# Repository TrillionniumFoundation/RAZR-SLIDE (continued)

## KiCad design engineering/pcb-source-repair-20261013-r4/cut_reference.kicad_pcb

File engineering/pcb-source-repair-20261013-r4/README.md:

# Controlled component sources and first-cut reference PCB, R4

`manufacturing_go=false`. `phone_complete_PCB=false`. This is an **unpowered single-cut bench reference**, not a released phone, pack protector, charging board, or complete safety circuit. No physical sample was energized or tested.

Eight actual PDFs were obtained from TI and checked by size, PDF page count and SHA-256. `primary_source_facts.json` identifies exact revisions and official URLs. Raw vendor PDFs remain outside the repository. The attempted EU Motorola L3 mirror returned HTTP 405; no complete OEM schematic was obtained from it.

The sources provide real reference schematics, BOMs, board layouts and package dimensions for TPS25947, BQ25620/BQ25622 and TUSB2E22. They do not establish equivalence to the OEM PMIH0104, OEM battery connectors, OLED or phone repeater. The BQ297xx threshold variants are different: BQ29700's nominal overvoltage threshold is 4.275 V and BQ29704's is 4.425 V. Neither can be chosen for an unknown cell chemistry. A low-side pack protector also requires every external reference to use protected PACK_N, never raw CELL_N.

For USB, the controlled TUSB2E22 datasheet and eUSB2 design guide distinguish 1.2-V eUSB2 signaling from conventional USB2. The proposed eUSB2 side uses a TI-recommended 85-ohm differential channel and a continuous reference; USB2 specifies 90 ohms. This research does not downgrade or qualify the project's USB interface. Exact OEM repeater, SoC configuration, flex stackup, full-motion eye, skew and leakage remain missing. TUSB2E22's RESETB must respect its 1.8-V interface; it is not a direct 3.3-V GPIO connection.

## Actual repair

`cut_reference.kicad_sch` and `cut_reference.kicad_pcb` implement a real **TPS259470LRPW** first discharge cut. This exact variant is latch-off with adjustable OVLO and active current limit. TPS259470ARPW and TPS259474LRPW must not be substituted by name. AUXOFF pin 3 is an open-drain output; the owned R4 symbol corrects the R3 research symbol's input classification while retaining R3 unchanged.

The editable board is 29 × 24 × 1.6 mm with 15 annotated items, 30 unique schematic-to-board physical pins, 34 copper pads and 47 routed segments. The nominal RPW0010A corner L lands are represented by overlapping same-number copper rectangles. Their nominal extents come from drawing 4225183/A; their square corners and full-area paste differ from TI's R0.05 and 82/93% example stencil. These deviations, passive 0805 lands and all actual component MPNs require assembly/DFM qualification.

Bench hypotheses are explicit: 2.7–4.4 V input from an isolated laboratory source, external 3.3-V enable, 10-kohm default-off EN resistor, 1.69-kohm ILM resistor and 10-nF slew capacitor. The datasheet equation gives about 1.973 A nominal current limit, with the stated device tolerance; this is not a measured current rating or a phone selection. Input/output capacitors and current-carrying copper have not been thermally qualified. There is no actual phone control supply, pack protector, second cut, receiver, return diagnosis, charge path or USB path on this board. Schottky/TVS protection and source/load transient bounds remain unqualified. No cell node enters this board's net map.

## Native evidence

- Main/qian-qi: actual KiCad 7.0.11, one fresh `pcbnew` process per serialized board. Initial V1 reported **37 DRC violations**, including genuine VIN/GND and FLT/VIN copper conflicts, hole clearances and library/silkscreen defects. These source bytes and complete reports remain in the V1 archives. V2 physically relocates the capacitor, control traces and ground vias and corrects the library; DRC, unconnected pads and footprint errors are all **0** under unchanged 0.1-mm copper / 0.25-mm hole rules. No rule exclusions were added.
- Removing the ILM route from the same V2 board gives one dangling-track warning and **one actual unconnected pad**. The helper's process exit 0 only means it produced the report; the report's counts govern acceptance.
- Pocket4: actual KiCad 9.0.8 XML export and ERC exit 0, with **0 violations at all severities**. An independent reader matches all 30 unique board/schematic pins and all 10 exact-variant pin functions. TP1/TP2 explicitly represent external isolated laboratory power/reference, not implemented phone regulators.
- Main: actual native Gerber, drill, placement, SVG, board-only STEP and schematic exports exit 0. The seven Gerber layers, PTH/NPTH drill files and seven SMD placement rows are preserved under `native_main/v2/exports`. Validated source bytes remain unchanged before/after export.
- Cloud: the entire exported STEP root is independently checked using the existing strict payload validator. It has one valid positive solid, 29 × 24 × 1.6-mm bounds and 1107.1660182454489 mm³ volume, matching the board with eight 0.8-mm pad holes. KiCad7's STEP omits the seven via bores and every unselected component 3D model. It is **not a full assembly** or a fit/thermal/insulation certificate.

`operator_process_receipts.json` retains native process results, child results and runtime failures. Pocket4's KiCad9 PCB plugin originally lacked OCC dependencies. Private dependency download attempts timed out; KiCad9 PCB DRC was not claimed. The actual board DRC/exports instead use the existing native KiCad7 engine on Main. A shell ending with `mkdir` and a Python report wrapper may exit 0 despite an earlier child failure; those failures remain visible. Full reports were recovered in version-pinned binary archives and checked by whole-file SHA-256.

`copper_only_preview.png` was visually checked against the native SVG. `pcb_preview.png` preserves the dense native F.Fab overlay for inspection; it is not an assembly drawing. The native editable schematic remains the authoritative connection drawing. Inkscape's startup GtkRecentManager warning was observed with successful exit 0.

The complete phone PCB, controlled OLED/FPC input, real assembly and physical capture/retraction/battery/USB/OLED qualifications remain open. No supplier message, NDA, order or production release was submitted. Fixed product constraints remain equal A/B external size, one approximately 7-inch OLED, 79.75-mm upward stroke and 8.2-mm normal seating, A battery priority and **4700-mAh total system target**.

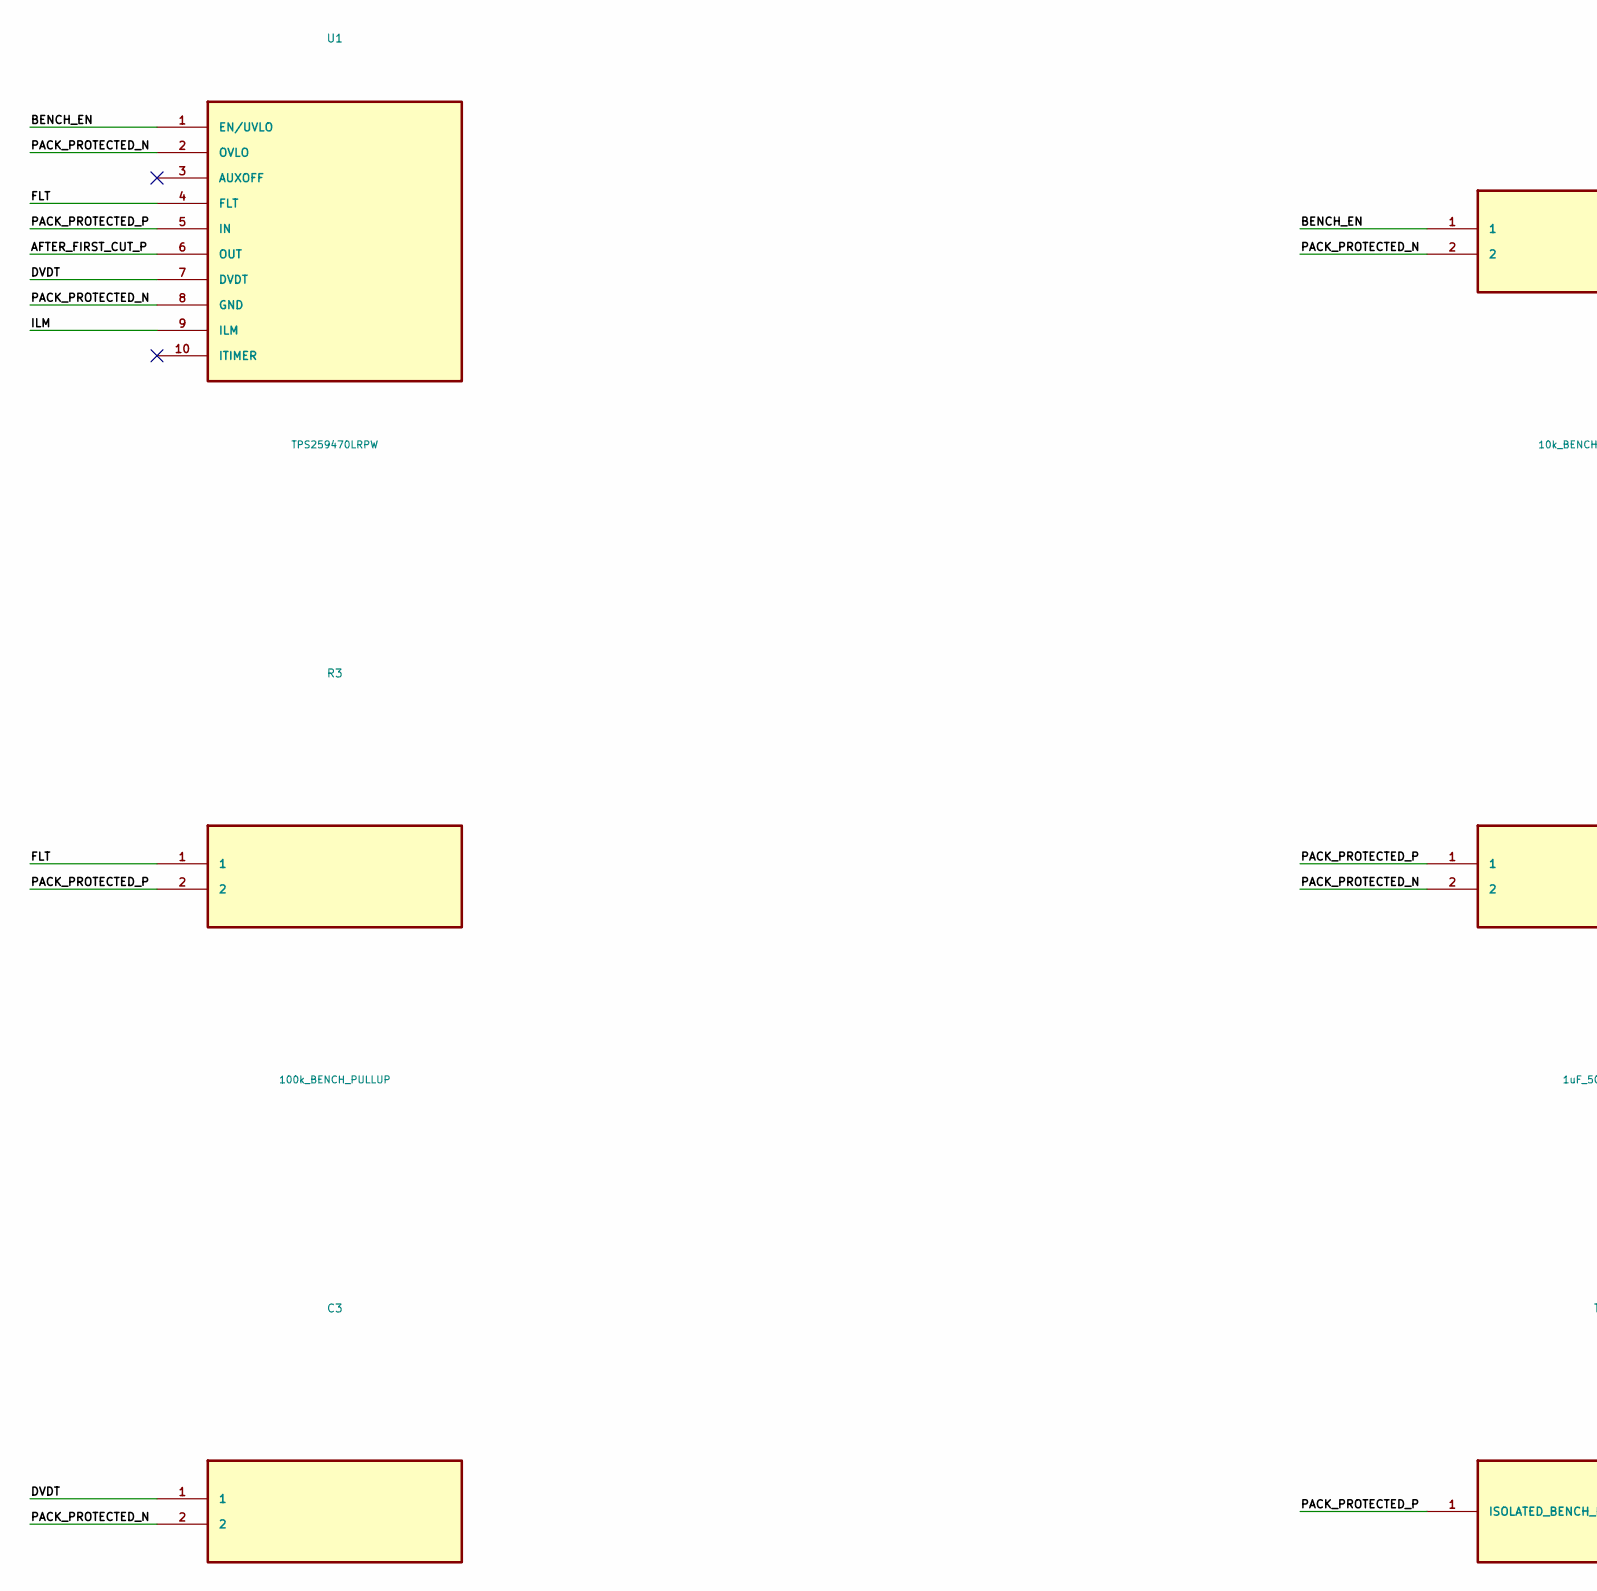
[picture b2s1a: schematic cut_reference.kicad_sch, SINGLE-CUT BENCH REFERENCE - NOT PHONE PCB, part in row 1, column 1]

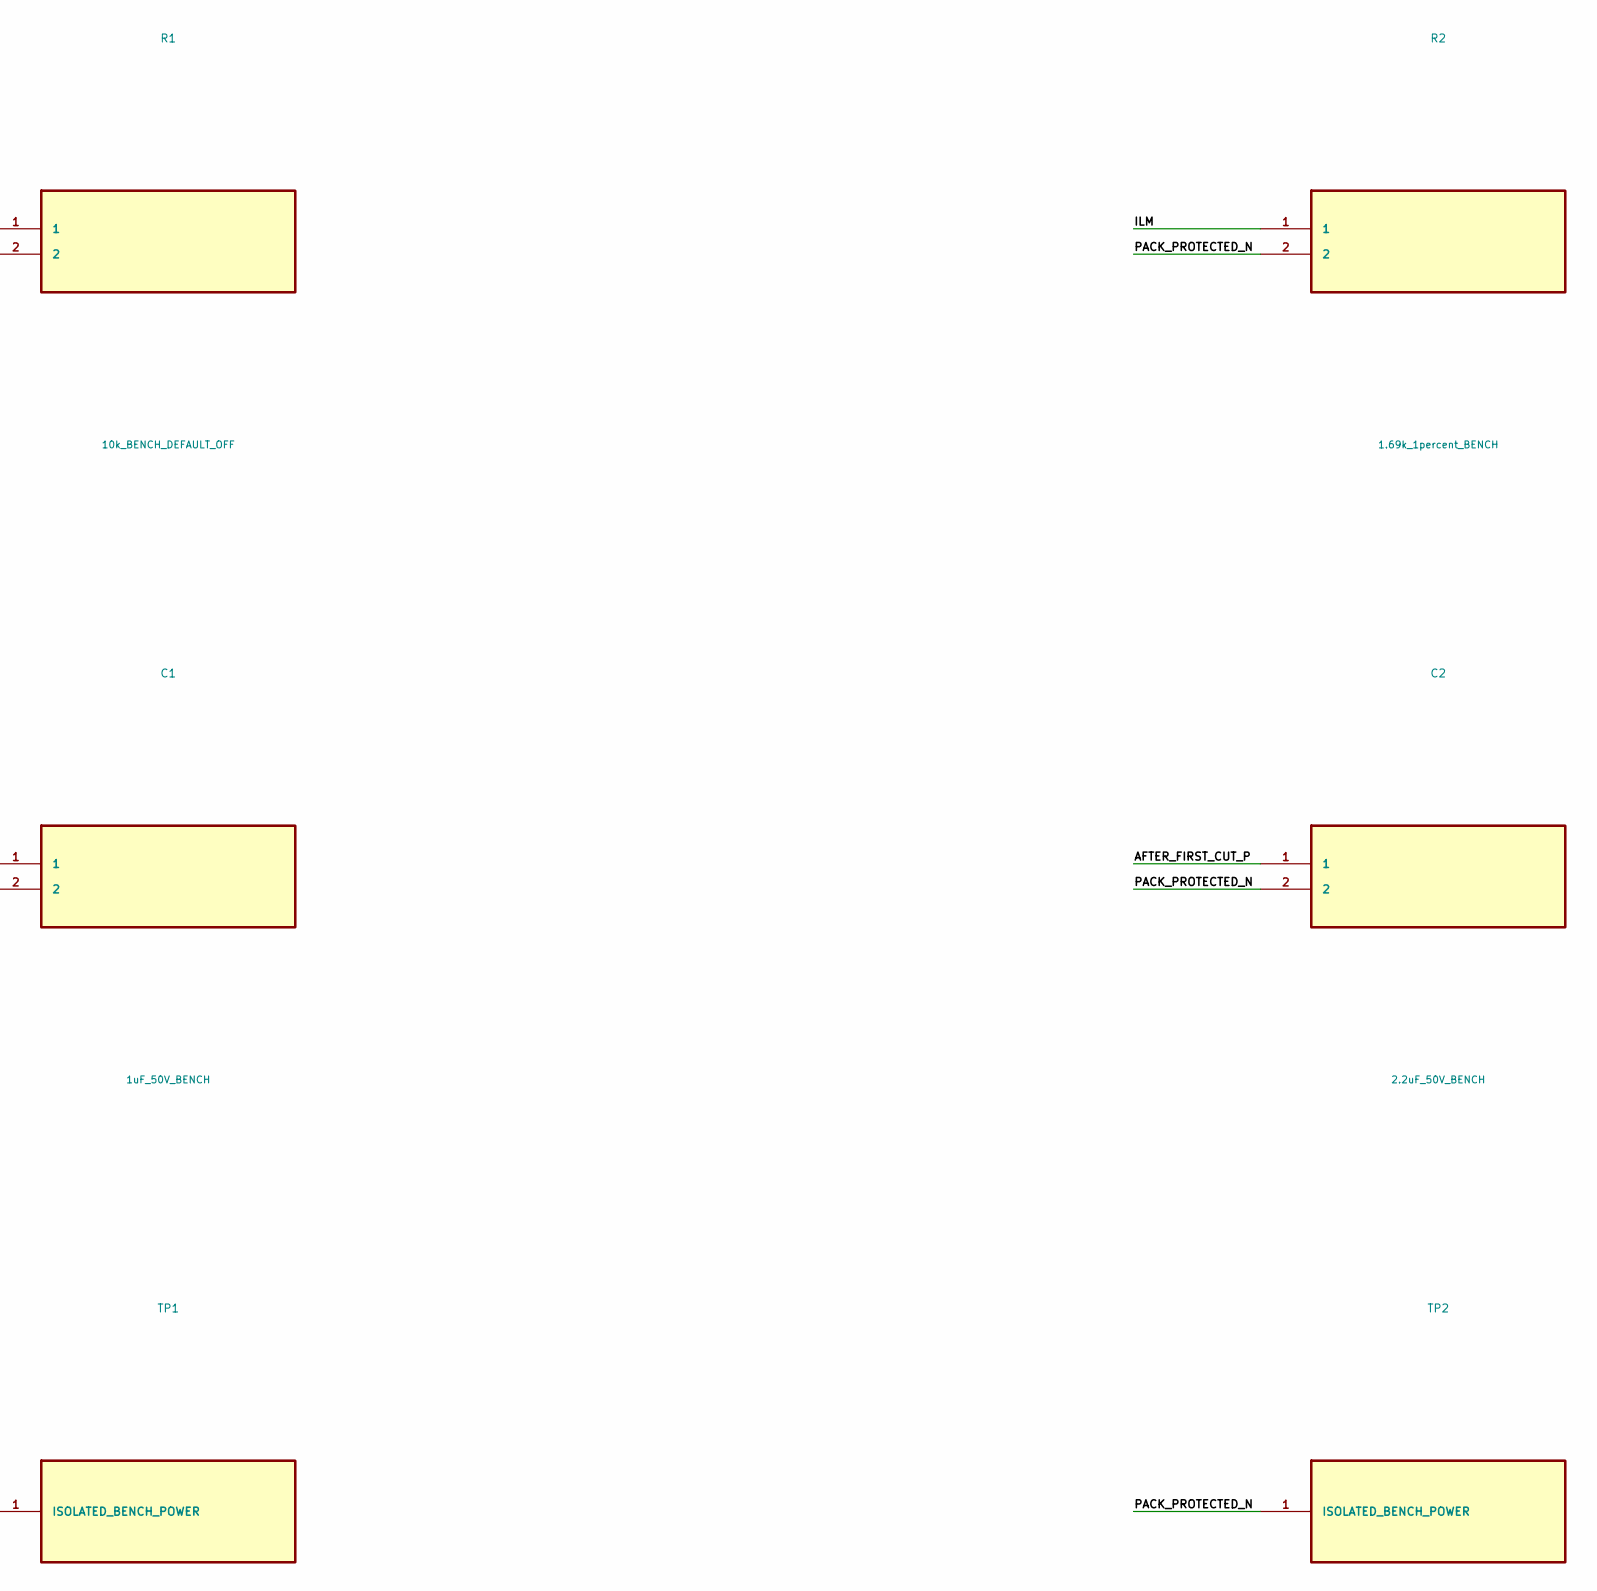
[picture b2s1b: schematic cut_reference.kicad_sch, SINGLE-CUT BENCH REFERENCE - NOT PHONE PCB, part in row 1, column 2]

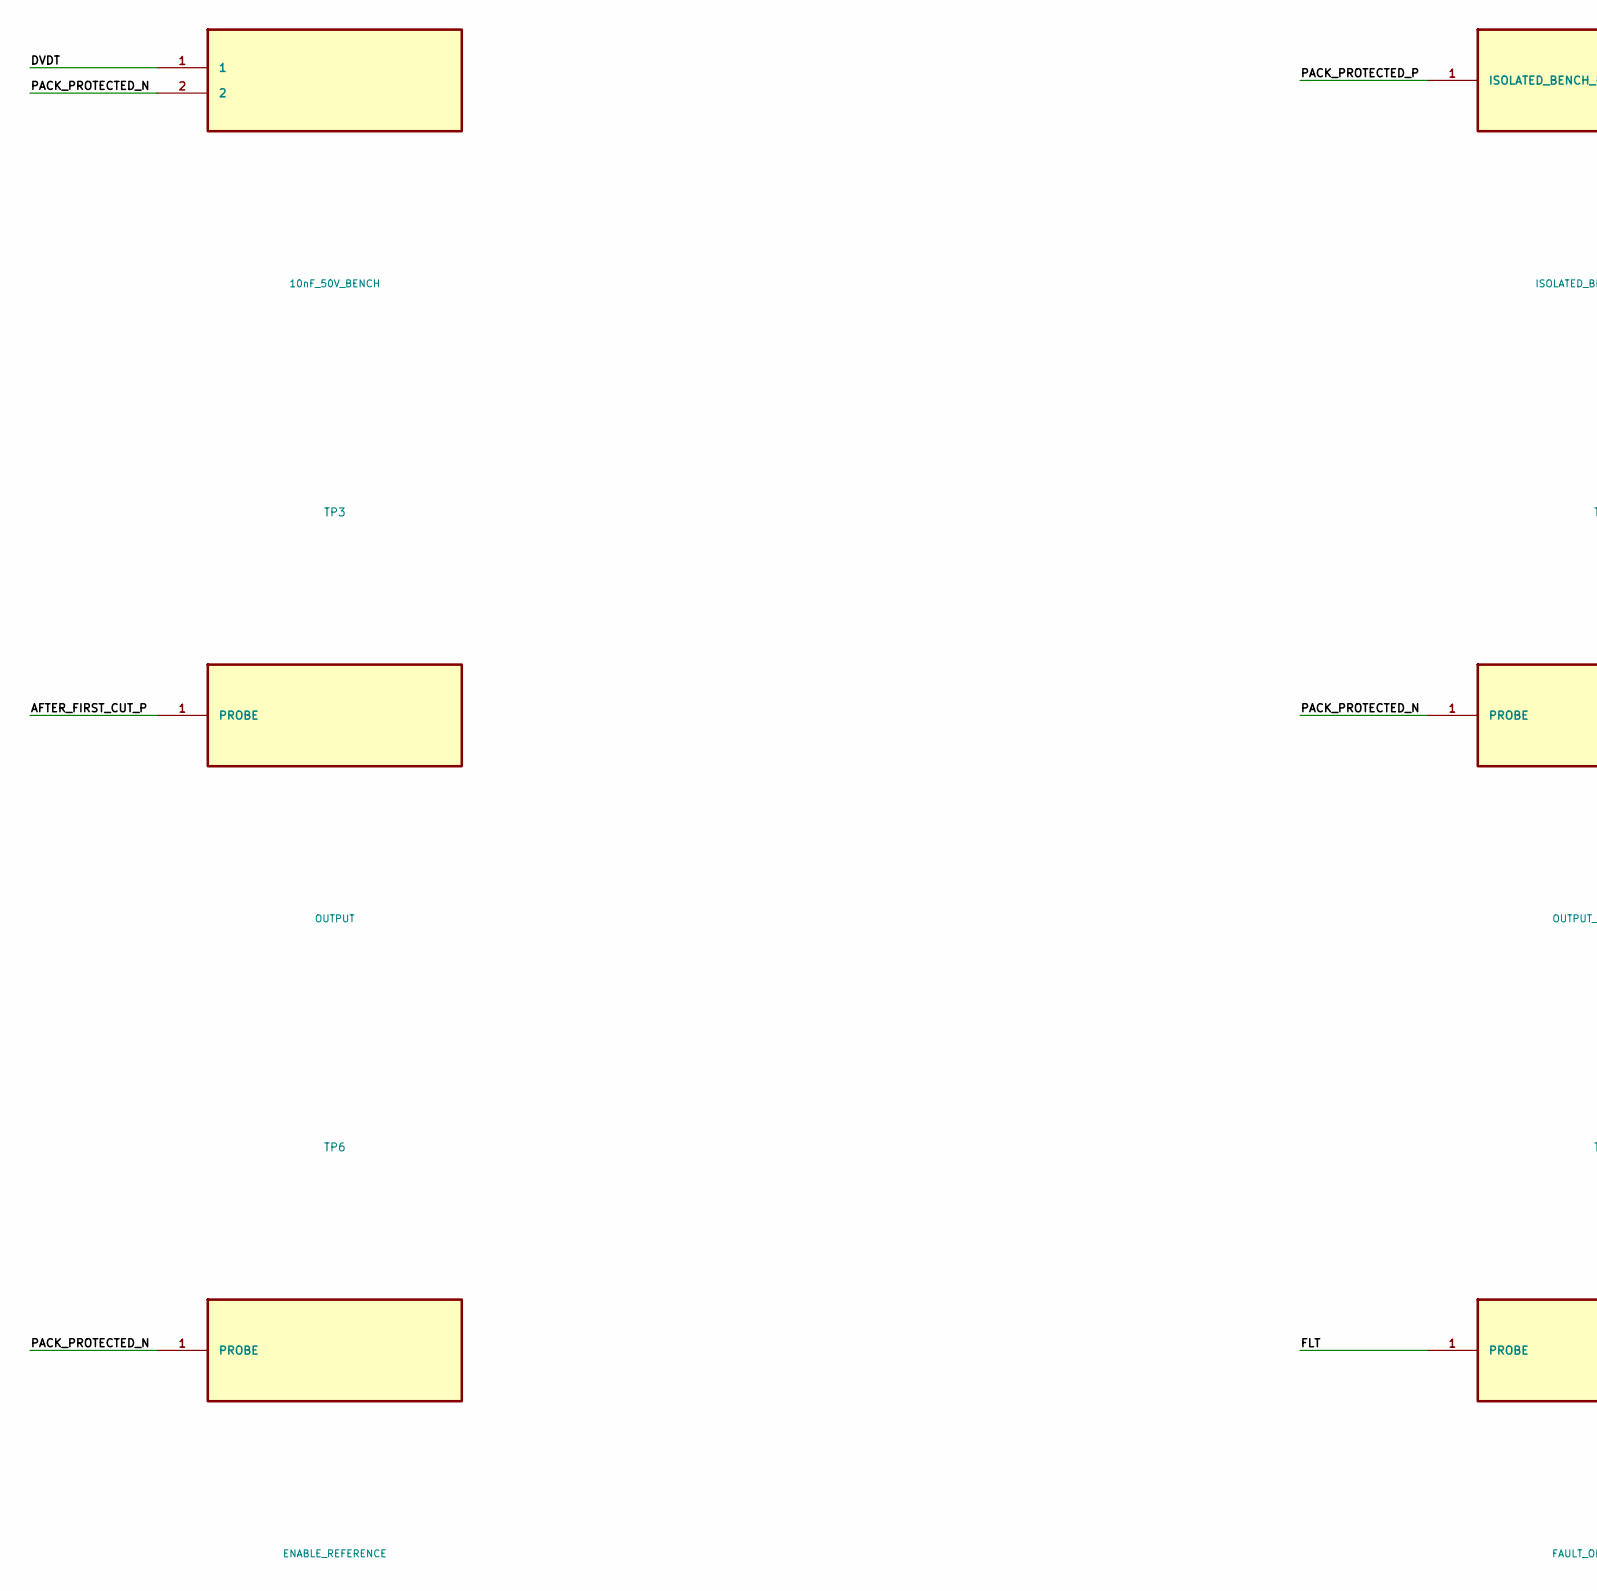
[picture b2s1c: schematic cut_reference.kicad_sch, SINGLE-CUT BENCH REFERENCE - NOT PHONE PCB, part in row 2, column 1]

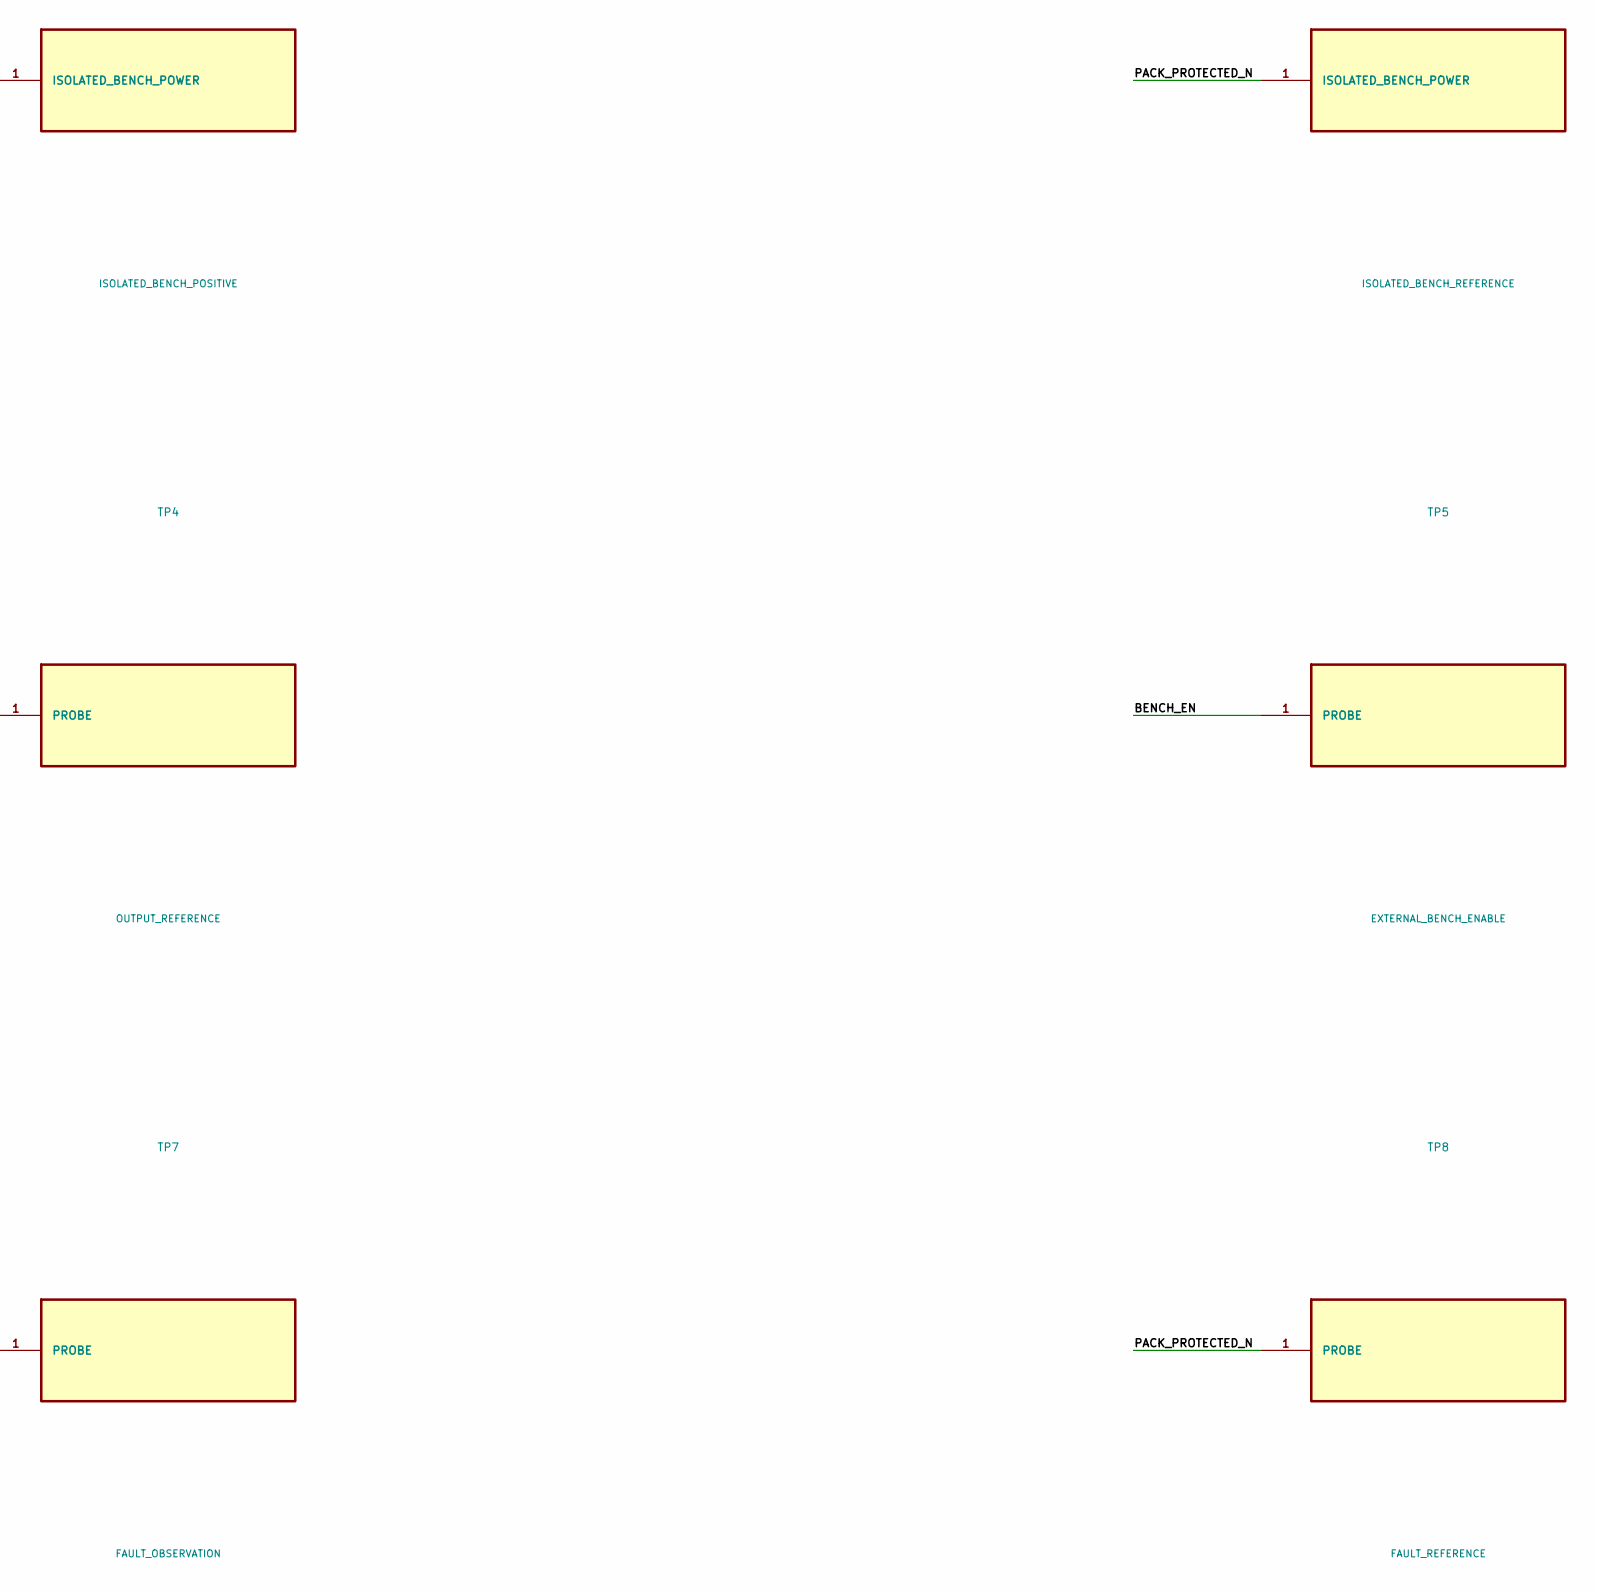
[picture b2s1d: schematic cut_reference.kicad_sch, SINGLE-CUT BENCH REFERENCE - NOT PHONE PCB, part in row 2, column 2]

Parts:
C1: 1uF_50V_BENCH; Passive_0805_BENCH
C2: 2.2uF_50V_BENCH; Passive_0805_BENCH
C3: 10nF_50V_BENCH; Passive_0805_BENCH
R1: 10k_BENCH_DEFAULT_OFF; Passive_0805_Vertical_BENCH
R2: 1.69k_1percent_BENCH; Passive_0805_BENCH
R3: 100k_BENCH_PULLUP; Passive_0805_BENCH
TP1: ISOLATED_BENCH_POSITIVE; Probe_1p8mm
TP2: ISOLATED_BENCH_REFERENCE; Probe_1p8mm
TP3: OUTPUT; Probe_1p8mm
TP4: OUTPUT_REFERENCE; Probe_1p8mm
TP5: EXTERNAL_BENCH_ENABLE; Probe_1p8mm
TP6: ENABLE_REFERENCE; Probe_1p8mm
TP7: FAULT_OBSERVATION; Probe_1p8mm
TP8: FAULT_REFERENCE; Probe_1p8mm
U1: TPS259470LRPW; RPW0010A_OWNED_NOMINAL

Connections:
AFTER_FIRST_CUT_P: C2.1, TP3.1, U1.6 (OUT)
BENCH_EN: R1.1, TP5.1, U1.1 (EN/UVLO)
DVDT: C3.1, U1.7 (DVDT)
FLT: R3.1, TP7.1, U1.4 (FLT)
ILM: R2.1, U1.9 (ILM)
PACK_PROTECTED_N: C1.2, C2.2, C3.2, R1.2, R2.2, TP2.1, TP4.1, TP6.1, TP8.1, U1.2 (OVLO), U1.8 (GND)
PACK_PROTECTED_P: C1.1, R3.2, TP1.1, U1.5 (IN)

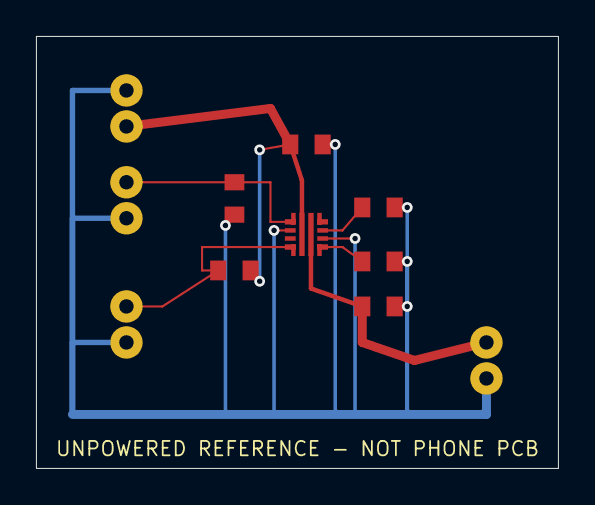
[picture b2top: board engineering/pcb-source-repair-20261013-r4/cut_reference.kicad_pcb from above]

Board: 2 copper layers, 29.0 x 24.0 mm, 15 parts (0 on the bottom side), 7 nets.

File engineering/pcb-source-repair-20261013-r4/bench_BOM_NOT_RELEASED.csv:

ref,part,value,footprint,MPN_selected_for_phone,physical_qualified
U1,TPS259470LRPW,TPS259470LRPW,RPW0010A_OWNED_NOMINAL,False,False
R1,R,10k_BENCH_DEFAULT_OFF,Passive_0805_Vertical_BENCH,False,False
R2,R,1.69k_1percent_BENCH,Passive_0805_BENCH,False,False
R3,R,100k_BENCH_PULLUP,Passive_0805_BENCH,False,False
C1,C,1uF_50V_BENCH,Passive_0805_BENCH,False,False
C2,C,2.2uF_50V_BENCH,Passive_0805_BENCH,False,False
C3,C,10nF_50V_BENCH,Passive_0805_BENCH,False,False
TP1,BenchSource,ISOLATED_BENCH_POSITIVE,Probe_1p8mm,False,False
TP2,BenchSource,ISOLATED_BENCH_REFERENCE,Probe_1p8mm,False,False
TP3,Probe,OUTPUT,Probe_1p8mm,False,False
TP4,Probe,OUTPUT_REFERENCE,Probe_1p8mm,False,False
TP5,Probe,EXTERNAL_BENCH_ENABLE,Probe_1p8mm,False,False
TP6,Probe,ENABLE_REFERENCE,Probe_1p8mm,False,False
TP7,Probe,FAULT_OBSERVATION,Probe_1p8mm,False,False
TP8,Probe,FAULT_REFERENCE,Probe_1p8mm,False,False

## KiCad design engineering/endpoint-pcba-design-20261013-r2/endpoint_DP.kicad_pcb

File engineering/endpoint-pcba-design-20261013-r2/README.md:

# BM28 static continuity coupon PCBA candidates

Two actual KiCad schematic/PCB projects route every independent BM28 coordinate
site to a probe hole. Native KiCad 7.0.11 loads both boards, reports zero DRC
violations, zero unconnected pads and zero footprint errors, and exports the
research Gerbers, drills, placement and BOM. Native schematic XML and native
board data independently agree on all 26 electrical nets per board. This is a
passive continuity-coupon design candidate, not the complete phone PCB.
Independent pocket4 KiCad 9.0.8 native ERC also reports zero violations on both
schematics after a real off-grid failure was corrected.

`manufacturing_go=false` and `coupon_fabrication_go=false`. Material, copper
weight, soldermask process, mating orientation and real assembly qualification
remain unverified. Nothing was ordered, fabricated, energized or measured on a
physical coupon in this work.

## Actual source and output files

Open `endpoint_DP.kicad_pro` or `endpoint_DS.kicad_pro`; each has a native
`.kicad_sch`, `.kicad_pcb`, local footprint table and owned symbol library. The
schematic contains one connector and 26 passive probe features. Probe features
are PCB copper and plated holes, not 26 discrete parts to purchase.

| Design feature | Each board |
| --- | ---: |
| Board outline, research hypothesis | 40 x 36 mm |
| Thickness, research hypothesis | 0.8 mm |
| Copper layers | 2 |
| Signal coordinate sites | 24 |
| Fitting terminal identities | 2 |
| Connector copper lands | 28 |
| Probe holes / copper features | 26 / 26 |
| Probe drill / pad diameter | 0.5 / 1.0 mm |
| Asymmetric fixture datum NPTH | 3 x 2.0 mm |
| Total native pad objects, including NPTH | 57 |
| Native track segments | 80, on F.Cu |
| Proposed minimum clearance / signal trace | 0.10 / 0.10 mm |

The 26 plated probe holes expose copper on both faces, allowing access from the
outside faces after two boards mate. A first layout with only front-side probe
pads was corrected because the inward faces would impede probing. No impedance,
current capability, high-speed operation or manufacturing process is qualified
by the above dimensions.

The two footprint copies in `RAZR_ENDPOINT_RESEARCH.pretty` are byte-identical
to the frozen prior endpoint source. `RAZR_ENDPOINT_ASSEMBLY.pretty` changes
only research BOM/placement exclusion flags. Board-instance reference text and
position are annotations; nominal copper, independent stencil rectangles and
the DS under-body copper/track/via/pad keepout stay unchanged. The DS keepout is
transformed into the actual board datum and checked by the native engine at
`[97.635, 99.410, 4.730, 1.180]` mm bounding rectangle. DP's 7.0 x 1.9-mm
minimum no-obstruction drawing is preserved, including its distinction from
an all-layer copper prohibition through its own lands.

## Coordinate identity and assembly datum

`C01` through `C26` mean continuity only. The supplier provides no pin-1
designation for these mechanically unpolarized connectors. `S_NEG_00` through
`S_POS_11`, `P_L` and `P_R` are our coordinate IDs, never invented supplier pin
numbers or Motorola net assignments. Two lands on each fitting share one
terminal ID. For example, our chosen pairing maps DP `S_NEG_00` to DS
`S_POS_00`; DP TP01 and DS TP13 both carry C01. All 26 pairings and actual probe
IDs are in `mating_site_map.json`.

The upper DP board uses the derived X-axis 180-degree transform
`diag(1,-1,-1)` with nominal 0.6-mm mating-plane translation. Native PCB-read
hole coordinates match all three DS datum holes under that transform and fail
the opposite Y-axis 180-degree orientation. This is a fixture datum proposal:
matching locating pins and a physical assembly trial are still required.
Silkscreen or intrinsic connector polarity alone does not prevent mis-mating.
The nominal translation is not the entire installed stack height.

New Motorola service evidence identifies SCA8D57591 24-pin/H0.6-mm/pitch0.35-mm
receptacles but does not give a Hirose series part number. Equal pitch, height
and pin count do not prove BM28 compatibility. No OEM assignment was transferred
to this coupon. See `../controlled-input-recovery-20261013-r2` for that evidence.

## Native evidence and retained counterexamples

`native_pcba_receipt.json` contains engine-read pads, tracks, hole coordinates,
the DS rule area, native netlists and exact export hashes. `native_execution_proof.json`
records the authoritative remote process exit, log offsets and transferred
archive SHA-256. `verify_native_pcba.py` never imports the builder.

The real missing-route negative control reports an unconnected pad. The actual
C01-to-C02 copper bridge reports four fatal native errors, including 0.0000-mm
cross-net copper clearance. Native DRC's Boolean report-writing return was
never treated as a passing result; report contents must show zero violations.
The rejected native boards and reports are retained.
Each DRC now runs in its own fresh native process from a serialized board and
checks that the proposed 0.10-mm clearance / 0.25-mm hole rules actually load.
The in-memory multiple-board path produced only one mask error on the same
shorted board; independent reload restored the four fatal errors. The exact
engine cause is not established. Both reports remain available; no constraint
or negative-control assertion was relaxed to accept the incomplete check.

Other retained failures include the initial 83/84 DRC warnings, an incorrect
native API call, local/global net namespace mismatch, missing export directories,
and a verifier's wrong assumption about a KiCad version's short-error label.
SVG output exposed another real failure: PCB SVG output needs an explicit file
name; a directory argument returned zero without replacing an old preview.
Current verification requires separate native board and schematic files,
existence and unequal byte hashes. Stale parent-directory previews are retained
as `REJECTED_svg_stale_parent_*`.

`verify_exports.py` independently parses the actual Gerber stencil polygons and
PTH/NPTH coordinates, checks 24 signal plus four fitting rectangles, checks all
probe and datum holes against native PCB data, and verifies that placement
contains only J1. `independent_export_receipt.json` records these results. The
absolute native export uses `x=board_x, y=-board_y`; negative export Y is a
coordinate convention.

The KiCad7 CLI does not have an ERC command, so the KiCad7 receipt truthfully
records `native_ERC_executed=false`. `pocket4_ERC_receipt.json` and the two
`endpoint_*_native_ERC.json` files provide the separate actual KiCad9 ERC runs:
zero errors, warnings and exclusions on both schematics, exit zero, and all 13
frozen input SHA-256 values unchanged. The initial real ERC found 79 off-grid
warnings per board. Symbol origins, label anchors and wire ends were moved to
the standard 1.27-mm connection grid; board geometry and all 26 nets stayed
unchanged. The original 13 input files are preserved in
`REJECTED_ERC_offgrid_inputs_v1.tar.gz`; failure reports reside in the adjoining
qualification evidence. `ERC_INPUTS_FROZEN.json` binds the repaired inputs.
Actual rendered schematic review then found overlapping probe references and
values despite the zero ERC result. Row pitch was increased to 5.08 mm, duplicate
displayed pin numbers hidden, connector attributes moved outside the symbol,
and probe reference/value text placed in separate columns. Current native7
exact-net verification and current independent native9 ERC both pass on those
final readable source hashes. The earlier ERC-pass source package and the real
overlap SVG/PNG are retained. `verification_summary.json` binds the current
combined result; `visual_review.json` records inspection of both final native
schematics and both final native board images.

## Remaining physical and controlled-input blockers

The original DP 6.32-MIN versus guideline 6.32-MAX authority conflict and DS
paste-volume discrepancy remain unresolved. Nominal 0.08-mm stencil arithmetic
is not a process approval. Zero soldermask expansion is explicitly an unqualified
hypothesis, not a supplier recommendation. Actual board process capability,
reflow/inspection plan, mating force and orientation, locator fit, buffer/preload,
connector availability and physical continuity measurements remain absent.

The three datum holes do not qualify a moving FPC strain-release design. The
flex stack, copper neutral axis, clamping details, voltage/current assignments,
USB lane routing, batteries, OEM electronics and final phone PCB are not present
in this coupon. They remain separate unresolved engineering inputs.

## Reproduce

Generate candidates with `python3 build_pcba.py`. In qian-qi's previously
extracted KiCad7 runtime, set `LD_LIBRARY_PATH` and `PYTHONPATH` to its preserved
`extracted/usr/lib/x86_64-linux-gnu` and `extracted/usr/lib/python3/dist-packages`,
and set `RAZR_KICAD_CLI` to that runtime's `extracted/usr/bin/kicad-cli`.
Run `python3 verify_native_pcba.py`, then `python3 verify_exports.py`. These
scripts create only local engineering evidence and research export files.

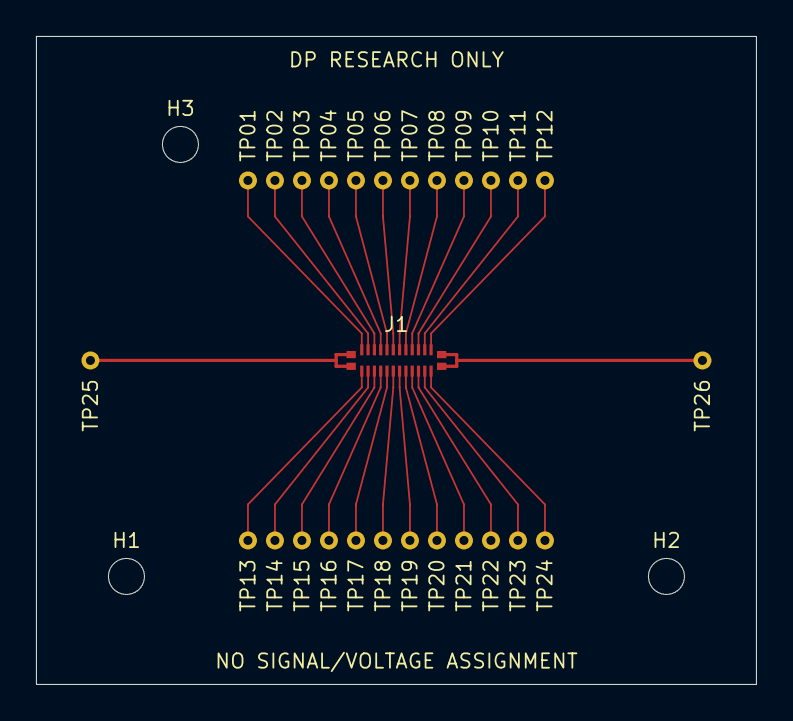
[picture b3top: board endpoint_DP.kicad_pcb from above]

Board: 2 copper layers, 40.0 x 36.0 mm, 30 parts (0 on the bottom side), 26 nets.

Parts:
H1, H2, H3: FIXTURE_DATUM_UNQUALIFIED; Datum_2mm_NPTH
J1: BM28_24DP_RESEARCH; Hirose_BM28B0.6-24DP_2-0.35V_53_RESEARCH_PHYSICAL_SITES
TP01: PROBE_ONLY_S_NEG_00; ProbePad_1mm_NO_PASTE
TP02: PROBE_ONLY_S_NEG_01; ProbePad_1mm_NO_PASTE
TP03: PROBE_ONLY_S_NEG_02; ProbePad_1mm_NO_PASTE
TP04: PROBE_ONLY_S_NEG_03; ProbePad_1mm_NO_PASTE
TP05: PROBE_ONLY_S_NEG_04; ProbePad_1mm_NO_PASTE
TP06: PROBE_ONLY_S_NEG_05; ProbePad_1mm_NO_PASTE
TP07: PROBE_ONLY_S_NEG_06; ProbePad_1mm_NO_PASTE
TP08: PROBE_ONLY_S_NEG_07; ProbePad_1mm_NO_PASTE
TP09: PROBE_ONLY_S_NEG_08; ProbePad_1mm_NO_PASTE
TP10: PROBE_ONLY_S_NEG_09; ProbePad_1mm_NO_PASTE
TP11: PROBE_ONLY_S_NEG_10; ProbePad_1mm_NO_PASTE
TP12: PROBE_ONLY_S_NEG_11; ProbePad_1mm_NO_PASTE
TP13: PROBE_ONLY_S_POS_00; ProbePad_1mm_NO_PASTE
TP14: PROBE_ONLY_S_POS_01; ProbePad_1mm_NO_PASTE
TP15: PROBE_ONLY_S_POS_02; ProbePad_1mm_NO_PASTE
TP16: PROBE_ONLY_S_POS_03; ProbePad_1mm_NO_PASTE
TP17: PROBE_ONLY_S_POS_04; ProbePad_1mm_NO_PASTE
TP18: PROBE_ONLY_S_POS_05; ProbePad_1mm_NO_PASTE
TP19: PROBE_ONLY_S_POS_06; ProbePad_1mm_NO_PASTE
TP20: PROBE_ONLY_S_POS_07; ProbePad_1mm_NO_PASTE
TP21: PROBE_ONLY_S_POS_08; ProbePad_1mm_NO_PASTE
TP22: PROBE_ONLY_S_POS_09; ProbePad_1mm_NO_PASTE
TP23: PROBE_ONLY_S_POS_10; ProbePad_1mm_NO_PASTE
TP24: PROBE_ONLY_S_POS_11; ProbePad_1mm_NO_PASTE
TP25: PROBE_ONLY_P_L; ProbePad_1mm_NO_PASTE
TP26: PROBE_ONLY_P_R; ProbePad_1mm_NO_PASTE

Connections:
C01: J1.S_NEG_00, TP01.1
C02: J1.S_NEG_01, TP02.1
C03: J1.S_NEG_02, TP03.1
C04: J1.S_NEG_03, TP04.1
C05: J1.S_NEG_04, TP05.1
C06: J1.S_NEG_05, TP06.1
C07: J1.S_NEG_06, TP07.1
C08: J1.S_NEG_07, TP08.1
C09: J1.S_NEG_08, TP09.1
C10: J1.S_NEG_09, TP10.1
C11: J1.S_NEG_10, TP11.1
C12: J1.S_NEG_11, TP12.1
C13: J1.S_POS_00, TP13.1
C14: J1.S_POS_01, TP14.1
C15: J1.S_POS_02, TP15.1
C16: J1.S_POS_03, TP16.1
C17: J1.S_POS_04, TP17.1
C18: J1.S_POS_05, TP18.1
C19: J1.S_POS_06, TP19.1
C20: J1.S_POS_07, TP20.1
C21: J1.S_POS_08, TP21.1
C22: J1.S_POS_09, TP22.1
C23: J1.S_POS_10, TP23.1
C24: J1.S_POS_11, TP24.1
C25: J1.P_L, TP25.1
C26: J1.P_R, TP26.1

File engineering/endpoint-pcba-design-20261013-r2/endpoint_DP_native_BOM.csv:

reference,value,footprint,procurement_role
J1,BM28_24DP_COORDINATE_SITES,RAZR_ENDPOINT_RESEARCH:Hirose_BM28B0.6-24DP_2-0.35V_53_RESEARCH_PHYSICAL_SITES,connector only
TP01,PROBE_S_NEG_00,Owned_Coupon:ProbePad_1mm_NO_PASTE,PCB probe feature; no discrete part
TP02,PROBE_S_NEG_01,Owned_Coupon:ProbePad_1mm_NO_PASTE,PCB probe feature; no discrete part
TP03,PROBE_S_NEG_02,Owned_Coupon:ProbePad_1mm_NO_PASTE,PCB probe feature; no discrete part
TP04,PROBE_S_NEG_03,Owned_Coupon:ProbePad_1mm_NO_PASTE,PCB probe feature; no discrete part
TP05,PROBE_S_NEG_04,Owned_Coupon:ProbePad_1mm_NO_PASTE,PCB probe feature; no discrete part
TP06,PROBE_S_NEG_05,Owned_Coupon:ProbePad_1mm_NO_PASTE,PCB probe feature; no discrete part
TP07,PROBE_S_NEG_06,Owned_Coupon:ProbePad_1mm_NO_PASTE,PCB probe feature; no discrete part
TP08,PROBE_S_NEG_07,Owned_Coupon:ProbePad_1mm_NO_PASTE,PCB probe feature; no discrete part
TP09,PROBE_S_NEG_08,Owned_Coupon:ProbePad_1mm_NO_PASTE,PCB probe feature; no discrete part
TP10,PROBE_S_NEG_09,Owned_Coupon:ProbePad_1mm_NO_PASTE,PCB probe feature; no discrete part
TP11,PROBE_S_NEG_10,Owned_Coupon:ProbePad_1mm_NO_PASTE,PCB probe feature; no discrete part
TP12,PROBE_S_NEG_11,Owned_Coupon:ProbePad_1mm_NO_PASTE,PCB probe feature; no discrete part
TP13,PROBE_S_POS_00,Owned_Coupon:ProbePad_1mm_NO_PASTE,PCB probe feature; no discrete part
TP14,PROBE_S_POS_01,Owned_Coupon:ProbePad_1mm_NO_PASTE,PCB probe feature; no discrete part
TP15,PROBE_S_POS_02,Owned_Coupon:ProbePad_1mm_NO_PASTE,PCB probe feature; no discrete part
TP16,PROBE_S_POS_03,Owned_Coupon:ProbePad_1mm_NO_PASTE,PCB probe feature; no discrete part
TP17,PROBE_S_POS_04,Owned_Coupon:ProbePad_1mm_NO_PASTE,PCB probe feature; no discrete part
TP18,PROBE_S_POS_05,Owned_Coupon:ProbePad_1mm_NO_PASTE,PCB probe feature; no discrete part
TP19,PROBE_S_POS_06,Owned_Coupon:ProbePad_1mm_NO_PASTE,PCB probe feature; no discrete part
TP20,PROBE_S_POS_07,Owned_Coupon:ProbePad_1mm_NO_PASTE,PCB probe feature; no discrete part
TP21,PROBE_S_POS_08,Owned_Coupon:ProbePad_1mm_NO_PASTE,PCB probe feature; no discrete part
TP22,PROBE_S_POS_09,Owned_Coupon:ProbePad_1mm_NO_PASTE,PCB probe feature; no discrete part
TP23,PROBE_S_POS_10,Owned_Coupon:ProbePad_1mm_NO_PASTE,PCB probe feature; no discrete part
TP24,PROBE_S_POS_11,Owned_Coupon:ProbePad_1mm_NO_PASTE,PCB probe feature; no discrete part
TP25,PROBE_P_L,Owned_Coupon:ProbePad_1mm_NO_PASTE,PCB probe feature; no discrete part
TP26,PROBE_P_R,Owned_Coupon:ProbePad_1mm_NO_PASTE,PCB probe feature; no discrete part

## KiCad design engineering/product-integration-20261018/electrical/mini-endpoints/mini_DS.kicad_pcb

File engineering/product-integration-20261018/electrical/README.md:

# Rebuilt electrical evidence

This directory contains a new execution after loss of local 2026-10-18 output bytes. The new run, source identity, environment and artifact hashes are recorded in rebuild-receipt.json and artifact-index.json.

Source assembly SHA256: `695073e313dae45edbb7cf8c305d31c167b4e24e1731bf8be8f1a91a77dbd77b`. Source Git commit: `3eae4e7258814c7f5454937535d6c642dd51662f`.

Completed 49 moving states and 15 manual states; rejected 49 moving and 15 manual states. The three full endpoint/material STEP files each underwent the source generator's 41-solid reimport check; the standalone bench clamp contains eight solids. No phone assembly or manufacturing release is issued.

Native KiCad v4 checks were not rerun. The three regenerated PCB byte hashes match the retained v4 input boards; DRC, Gerber, drill and measured STEP-thickness evidence remains in the existing main checkout. No historical execution log or test result is relabeled as part of this execution.

See source-design-notes.md for the preserved design narrative, and research-BOM.csv for a newly derived two-end research bill of materials. These notes and material quantities are definitions, not physical stock or fabrication evidence. Actual donor identity, OEM pin mapping, FPC material qualification and installed phone circuitry remain unverified.

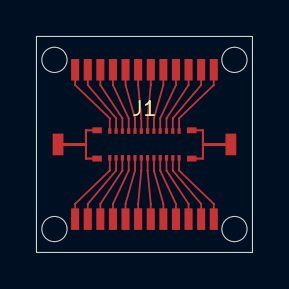
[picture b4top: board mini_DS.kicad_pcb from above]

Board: 2 copper layers, 12.0 x 12.0 mm, 31 parts (0 on the bottom side), 26 nets.

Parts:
H1, H2, H3, H4: 1.4mm_NPTH; M1_NPTH
J1: BM28_24DS_RESEARCH; Hirose_BM28B0.6-24DS_2-0.35V_53_RESEARCH_PHYSICAL_SITES
TP01: OWNED_S_POS_00; HAND_SOLDER_PAD_045x120
TP02: OWNED_S_POS_01; HAND_SOLDER_PAD_045x120
TP03: OWNED_S_POS_02; HAND_SOLDER_PAD_045x120
TP04: OWNED_S_POS_03; HAND_SOLDER_PAD_045x120
TP05: OWNED_S_POS_04; HAND_SOLDER_PAD_045x120
TP06: OWNED_S_POS_05; HAND_SOLDER_PAD_045x120
TP07: OWNED_S_POS_06; HAND_SOLDER_PAD_045x120
TP08: OWNED_S_POS_07; HAND_SOLDER_PAD_045x120
TP09: OWNED_S_POS_08; HAND_SOLDER_PAD_045x120
TP10: OWNED_S_POS_09; HAND_SOLDER_PAD_045x120
TP11: OWNED_S_POS_10; HAND_SOLDER_PAD_045x120
TP12: OWNED_S_POS_11; HAND_SOLDER_PAD_045x120
TP13: OWNED_S_NEG_00; HAND_SOLDER_PAD_045x120
TP14: OWNED_S_NEG_01; HAND_SOLDER_PAD_045x120
TP15: OWNED_S_NEG_02; HAND_SOLDER_PAD_045x120
TP16: OWNED_S_NEG_03; HAND_SOLDER_PAD_045x120
TP17: OWNED_S_NEG_04; HAND_SOLDER_PAD_045x120
TP18: OWNED_S_NEG_05; HAND_SOLDER_PAD_045x120
TP19: OWNED_S_NEG_06; HAND_SOLDER_PAD_045x120
TP20: OWNED_S_NEG_07; HAND_SOLDER_PAD_045x120
TP21: OWNED_S_NEG_08; HAND_SOLDER_PAD_045x120
TP22: OWNED_S_NEG_09; HAND_SOLDER_PAD_045x120
TP23: OWNED_S_NEG_10; HAND_SOLDER_PAD_045x120
TP24: OWNED_S_NEG_11; HAND_SOLDER_PAD_045x120
TP25: OWNED_P_L; HAND_SOLDER_PAD_060x120
TP26: OWNED_P_R; HAND_SOLDER_PAD_060x120

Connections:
C01: J1.S_POS_00, TP01.1
C02: J1.S_POS_01, TP02.1
C03: J1.S_POS_02, TP03.1
C04: J1.S_POS_03, TP04.1
C05: J1.S_POS_04, TP05.1
C06: J1.S_POS_05, TP06.1
C07: J1.S_POS_06, TP07.1
C08: J1.S_POS_07, TP08.1
C09: J1.S_POS_08, TP09.1
C10: J1.S_POS_09, TP10.1
C11: J1.S_POS_10, TP11.1
C12: J1.S_POS_11, TP12.1
C13: J1.S_NEG_00, TP13.1
C14: J1.S_NEG_01, TP14.1
C15: J1.S_NEG_02, TP15.1
C16: J1.S_NEG_03, TP16.1
C17: J1.S_NEG_04, TP17.1
C18: J1.S_NEG_05, TP18.1
C19: J1.S_NEG_06, TP19.1
C20: J1.S_NEG_07, TP20.1
C21: J1.S_NEG_08, TP21.1
C22: J1.S_NEG_09, TP22.1
C23: J1.S_NEG_10, TP23.1
C24: J1.S_NEG_11, TP24.1
C25: J1.P_L, TP25.1
C26: J1.P_R, TP26.1

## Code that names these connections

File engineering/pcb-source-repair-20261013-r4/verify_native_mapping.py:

"""Read the real native XML and PCB payload independently of their builder."""
import hashlib,json,re,sys,xml.etree.ElementTree as ET
from pathlib import Path
root=Path(sys.argv[1]) if len(sys.argv)>1 else Path(__file__).resolve().parent

def sexpr(src):
 toks=re.findall(r'"(?:\\.|[^"\\])*"|[()]|[^\s()]+',src); stack=[];cur=[]
 for t in toks:
  if t=='(':stack.append(cur);cur=[]
  elif t==')':old=cur;cur=stack.pop();cur.append(old)
  else:cur.append(json.loads(t) if t.startswith('"') else t)
 assert not stack and len(cur)==1
 return cur[0]
def kids(a,k):return [v for v in a if isinstance(v,list) and v and v[0]==k]
def one(a,k):return kids(a,k)[0]
board=sexpr((root/'cut_reference.kicad_pcb').read_text())
bmap={};duplicates=0
for fp in kids(board,'footprint'):
 ref=next(v[2] for v in kids(fp,'fp_text') if v[1]=='reference')
 for pad in kids(fp,'pad'):
  pn=pad[1];net=kids(pad,'net');net=net[0][2] if net else None
  key=(ref,pn)
  if key in bmap:assert bmap[key]==net;duplicates+=1
  bmap[key]=net
xml=ET.parse(root/'native.xml').getroot();xmap={}
for net in xml.findall('./nets/net'):
 name=net.attrib['name'].removeprefix('/')
 for node in net.findall('node'):xmap[(node.attrib['ref'],node.attrib['pin'])]=name
facts=json.loads((root/'reference_terminal_map.json').read_text())
count=0
for c in facts['components']:
 for i,net in enumerate(c['nets'],1):
  key=(c['ref'],str(i));assert key in bmap,(key,'missing PCB pad')
  assert bmap[key]==net,(key,'PCB',bmap[key],net)
  if net is not None:assert xmap[key]==net,(key,'XML',xmap.get(key),net)
  else:assert key not in xmap or xmap[key].startswith('unconnected-'),(key,xmap.get(key))
  count+=1
# Official exact-variant pin functions, independently transcribed from table 5-1.
pin_functions={1:'EN/UVLO',2:'OVLO',3:'AUXOFF',4:'FLT',5:'IN',6:'OUT',7:'DVDT',8:'GND',9:'ILM',10:'ITIMER'}
lib=sexpr((root/'OwnedCut.kicad_sym').read_text());u=next(s for s in kids(lib,'symbol') if s[1]=='TPS259470LRPW')
pins=kids(next(s for s in kids(u,'symbol') if s[1]=='TPS259470LRPW_1_1'),'pin')
for p in pins:
 n=int(one(p,'number')[1]);assert one(p,'name')[1]==pin_functions[n]
 if n in (3,4):assert p[1]=='open_collector'
assert len(pins)==10 and count==30
erc=json.loads((root/'ERC.json').read_text())
assert all(not sheet.get('violations') for sheet in erc.get('sheets',[])), 'ERC actual violations'
receipt={'native_XML_PCB_unique_pin_matches':count,'extra_same_number_L_land_rectangles':duplicates,'official_exact_variant_pin_functions_matched':10,'AUXOFF_and_FLT_types':'open_collector','raw_CELLP_CELLN_not_present':not any('CELL' in n for n in bmap.values() if n),'phone_complete_PCB':False,'manufacturing_go':False,'frozen_inputs':{n:hashlib.sha256((root/n).read_bytes()).hexdigest() for n in ['cut_reference.kicad_sch','cut_reference.kicad_pcb','OwnedCut.kicad_sym','reference_terminal_map.json']}}
(root/'independent_native_mapping.json').write_text(json.dumps(receipt,indent=2)+'\n')
print(json.dumps(receipt))
